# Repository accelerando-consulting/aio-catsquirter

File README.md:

# CatSquirter - a mosfet switching shield for pumps or other small loads

This project is a circuit board that allows one to control a high current
output using a Mostfet rather than a relay.  It is intended to stack atop the
Lolin D1 mini microcontroller board, or any other board that uses the D1 bus (such as 
Accelerando Redsoil (nRF52840) , Accelerano Bungan (nRF52833) or Accelerando Cowan (ESP32-C3).

It was originally created to drive a small submersible fountain pump in order to produce a brief
spray of water (harmless but surprising) to discourage a pet from scratching an item of furniture.

## How it works

Jumpers allow any of D0,D1,D5-D8 to be connected to the gate of the MOSFET.  When the corresponding pin is
HIGH, the MOSFET turns on and power flows to the PUMP socket. 

Another jumper controls the source of the power to the pump.   For a battery operated pump, fit a Lolin battery shield and
connect the battery to the catsquirter shield, then connect the second battery connector to the Lolin shield.   This
arrangement uses the high current available direct from a lithium battery to run the pump.

Alternatively, if your project is not battery powered, a jumper allows connecting the 5v or 3v3 pins from the
D1 stacking bus to the mosfet drain.  (Be careful not to use more current than your regulator can handle!).   In one
instance I'm using the 5v from the USB connecter to run a small vacuum pump.

Finally, if you have a higher voltage load (say, 12v), you could connect power to one of the battery headers (in which case DO NOT connect the second header to a battery shield!).

A LED will light when the pump fet is enabled.

## What can I do with it

* Water your indoor pot-plants.
* Control a low voltage cooling or ventilation fan
* Make a small drinking fountain for people or pets.
* Run a vacuum pump or fume extractor for soldering.
* Stack several of these (with different jumper settings on each one) to control several devices.
* Control low voltage LED lighting (up to 2A, for higher current lighting see Accelerando Jahlo).
* Control a heavy duty relay for more signifiant loads

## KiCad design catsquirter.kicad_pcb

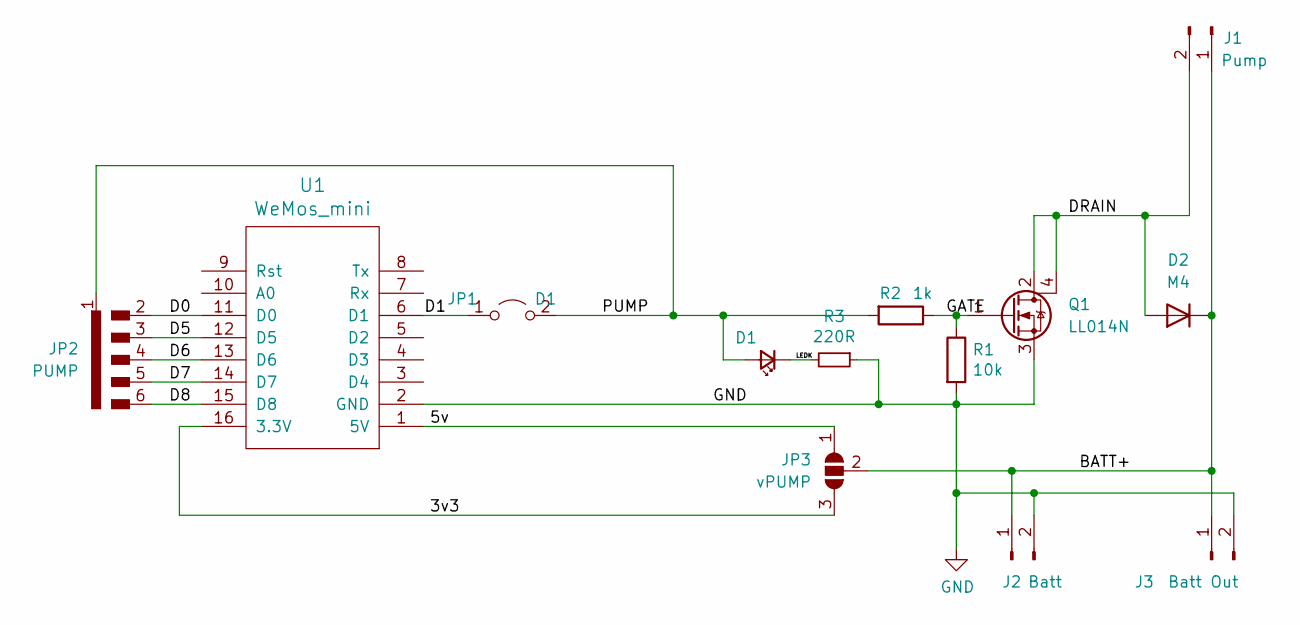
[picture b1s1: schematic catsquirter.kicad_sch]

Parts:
D1: LED_Small; LED_0805_2012Metric
D2: M4; D_SMB
J1: Pump; JST_XH_S02B-XH-A_02x2.50mm_Angled
J2: Batt; JST_XH_S02B-XH-A_02x2.50mm_Angled
J3: Batt Out; JST_XH_S02B-XH-A_02x2.50mm_Angled
JP1: D1; SolderJumper-2_P1.3mm_Open_RoundedPad1.0x1.5mm
JP2: PUMP; SolderJumper-5_P1.3mm_Open_Pad1.0x1.5mm
JP3: vPUMP; SolderJumper-3_P2.0mm_Open_TrianglePad1.0x1.5mm
Q1: LL014N; SOT-223
R1: 10k; R_0805_2012Metric
R2: 1k; R_0805_2012Metric
R3: 220R; R_0805_2012Metric
U1: WeMos_mini; wemos-d1-mini-connectors-only

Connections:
/3v3: JP3.3 (B), U1.16 (3.3V)
/5v: JP3.1 (A), U1.1 (5V)
/BATT+: D2.1 (K), J1.1, J2.1, J3.1, JP3.2 (C)
/D0: JP2.2 (A), U1.11 (D0)
/D1: JP1.1 (A), U1.6 (D1)
/D5: JP2.3 (B), U1.12 (D5)
/D6: JP2.4 (C), U1.13 (D6)
/D7: JP2.5 (D), U1.14 (D7)
/D8: JP2.6 (E), U1.15 (D8)
/DRAIN: D2.2 (A), J1.2, Q1.2 (D), Q1.4 (D)
/GATE: Q1.1 (G), R1.1, R2.1
/LEDK: D1.1 (K), R3.2
/PUMP: D1.2 (A), JP1.2 (B), JP2.1 (A), R2.2
GND: J2.2, J3.2, Q1.3 (S), R1.2, R3.1, U1.2 (GND)

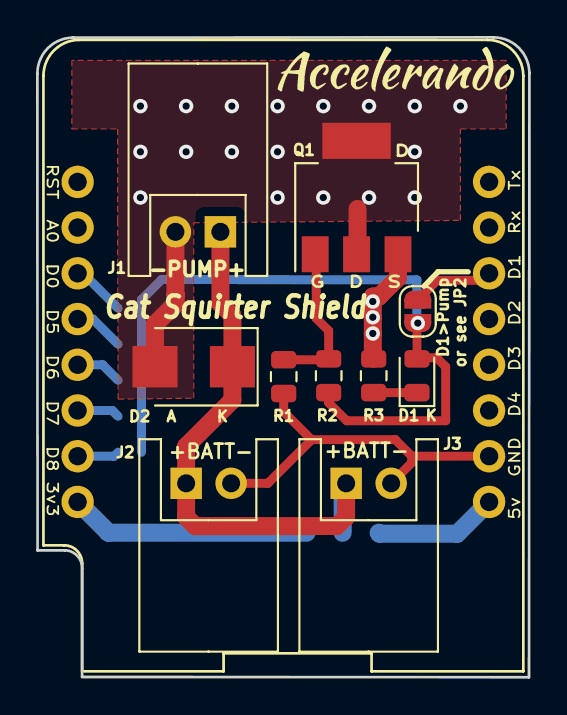
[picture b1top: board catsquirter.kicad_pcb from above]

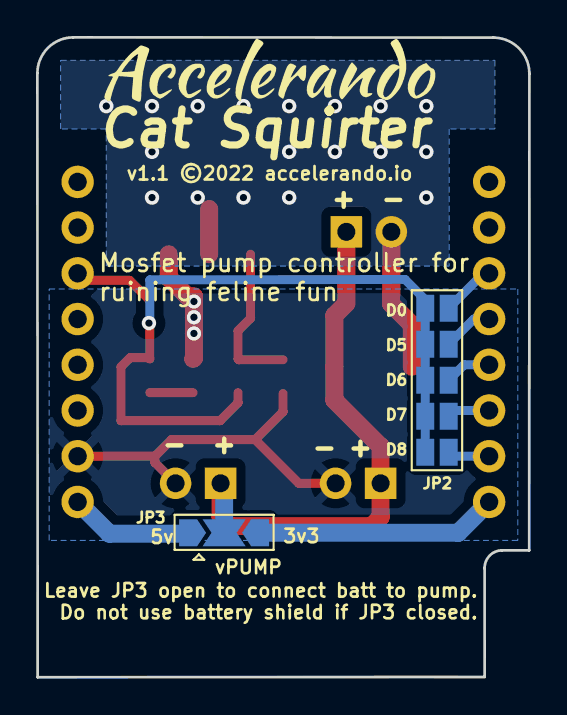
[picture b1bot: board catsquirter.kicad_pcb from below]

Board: 2 copper layers, 27.3 x 35.5 mm, 13 parts (2 on the bottom side), 14 nets.

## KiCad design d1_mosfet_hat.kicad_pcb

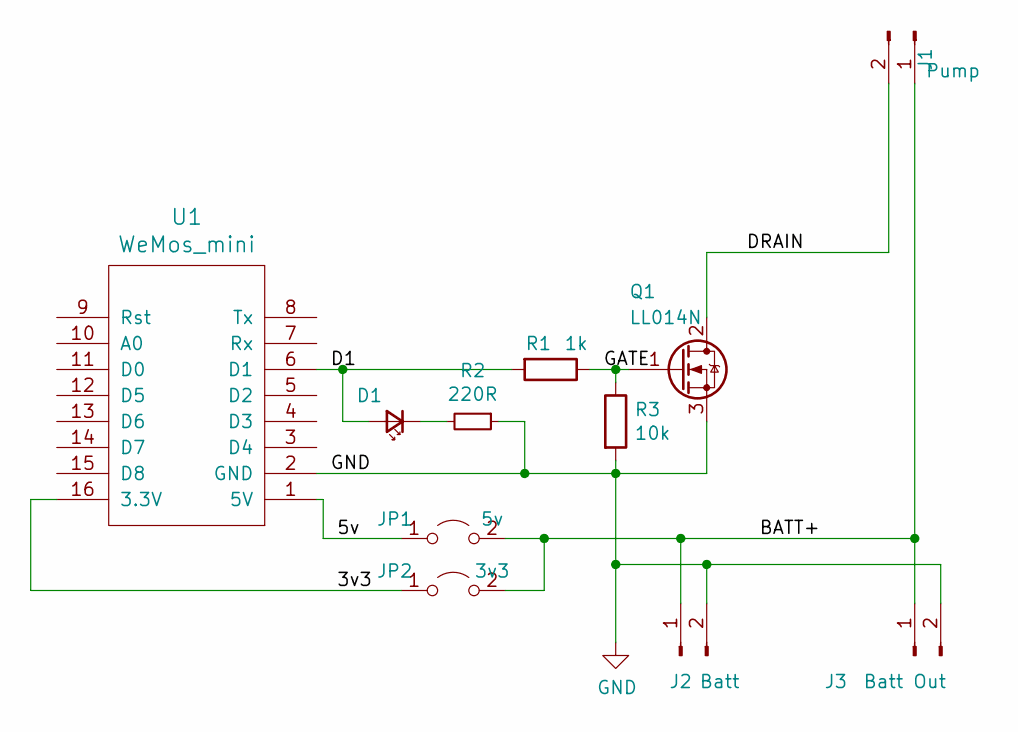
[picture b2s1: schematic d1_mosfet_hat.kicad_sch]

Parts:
D1: LED_Small; LED_0805_2012Metric
J1: Pump; JST_XH_S02B-XH-A_02x2.50mm_Angled
J2: Batt; JST_XH_S02B-XH-A_02x2.50mm_Angled
J3: Batt Out; JST_XH_S02B-XH-A_02x2.50mm_Angled
JP1: 5v; SolderJumper-2_P1.3mm_Open_RoundedPad1.0x1.5mm
JP2: 3v3; SolderJumper-2_P1.3mm_Open_RoundedPad1.0x1.5mm
Q1: LL014N; SOT-223
R1: 1k; R_0805_2012Metric
R2: 220R; R_0805_2012Metric
R3: 10k; R_0805_2012Metric
U1: WeMos_mini; wemos-d1-mini-connectors-only

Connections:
/3v3: JP2.1 (A), U1.16 (3.3V)
/5v: JP1.1 (A), U1.1 (5V)
/BATT+: J1.1, J2.1, J3.1, JP1.2 (B), JP2.2 (B)
/D1: D1.2 (A), R1.2, U1.6 (D1)
/DRAIN: J1.2, Q1.2 (D)
/GATE: Q1.1 (G), R1.1, R3.1
GND: J2.2, J3.2, Q1.3 (S), R2.1, R3.2, U1.2 (GND)
unnamed: D1.1 (K), R2.2

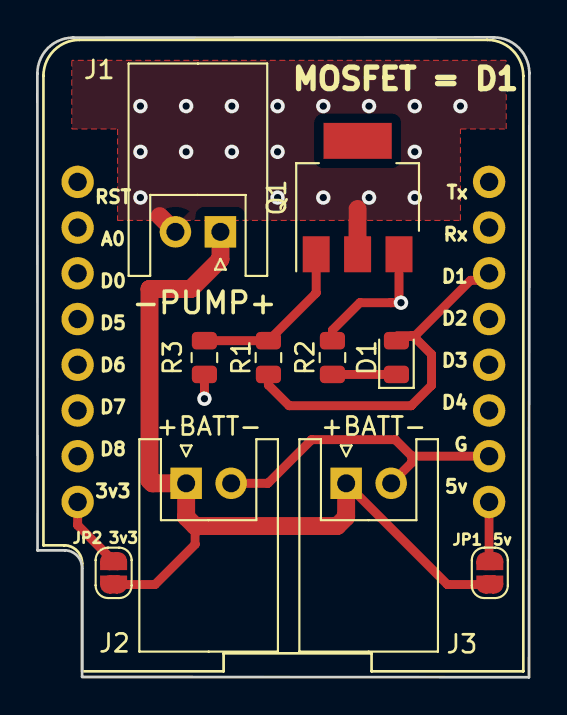
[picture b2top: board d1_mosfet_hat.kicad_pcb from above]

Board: 2 copper layers, 27.3 x 35.5 mm, 11 parts (0 on the bottom side), 8 nets.

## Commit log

2019-09-14 D1 shields for various client projects
2022-04-12 d1_mosfet shield v1
2022-04-12 Remove unwanted files
2022-12-03 Cat squirter v1.1 - add jumpers to use 5v or 3v power
2022-12-04 Add pin/volt jumpers. Rename project files d1_mosfet_hat -> catsquirter.
2022-12-04 Gerbers for catsquirter 1v1
2022-12-04 Add README

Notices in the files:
catsquirter.kicad_pcb:
v1.1 ©2022 accelerando.io
